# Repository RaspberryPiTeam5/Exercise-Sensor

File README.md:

This repository was created for a project using the raspberry pi. Files included are a schematic of the PCB used in conjunction with the pi along with the necessary files to run a GUI to plot outputs.  
Sensors used include:

1- Temperature Sensor

2- Moisture/Sweat Sensor

3- Pulse/Heart Rate Sensor  

The software requires the download of the qt4 and qwt libraries including:

   • qt4-dev-tools
   
   • libqt4-dev
   
   • libqwt-dev

To run the software:  
1- Clone the repository onto your pi with the following link: https://github.com/RaspberryPiTeam5/Exercise-Sensor  
2- build with the command "qmake" followed by "make"  
3- Run the program with "startx ./Exercise" (assuming no X is running whilst on an SSH).  
    
If you require any assistance with regards to this project, please contact either:  

Mustafa Miyasar - 2015221M@student.glasgow.ac.uk  
Roheel Arshad - 2018987A@student.glasgow.ac.uk
 
Please read the corresponding Wiki page for further information regarding this project.

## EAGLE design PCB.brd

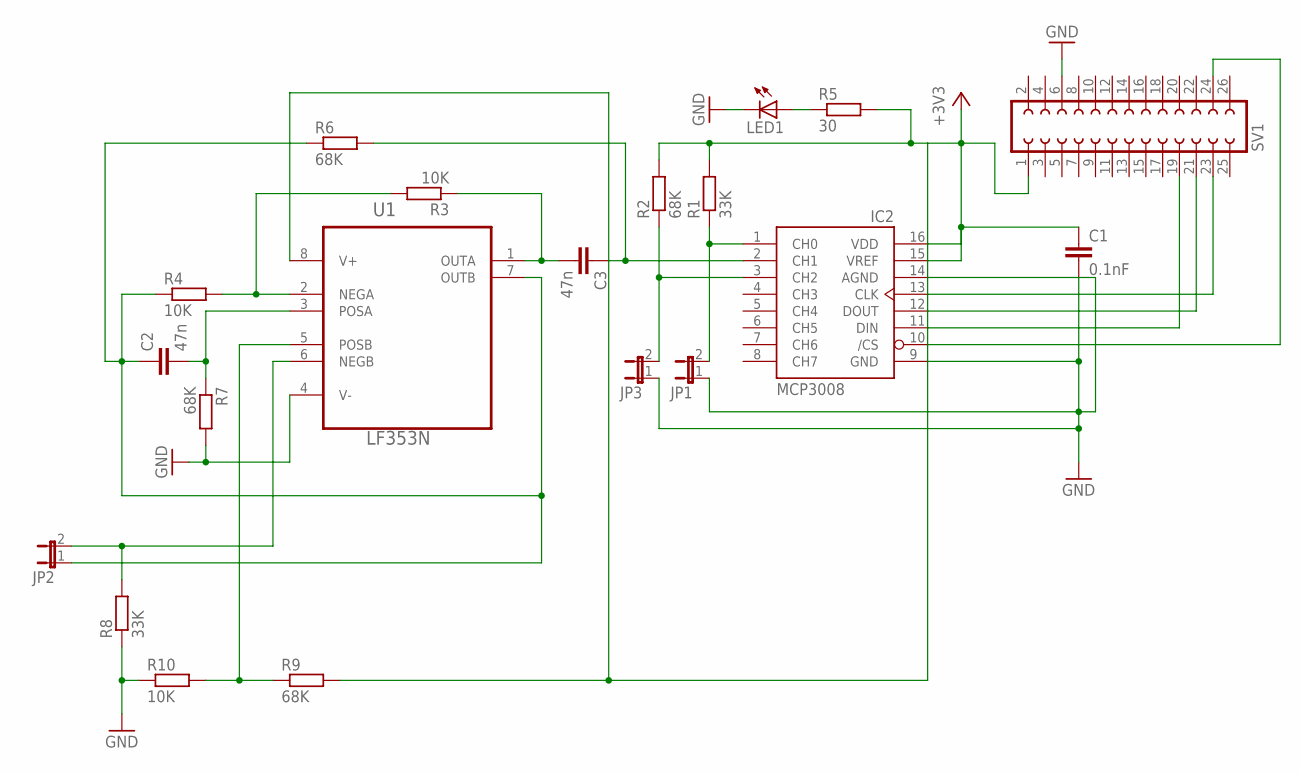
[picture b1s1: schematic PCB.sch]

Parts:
C1: 0.1nF; C050-035X075
C2, C3: 47n; C2.5-5
IC2: MCP3008; DIL16
JP1, JP2, JP3: JP1E; JP1
LED1: LED5MM
R1, R8: 33K; 0207/10
R2, R6, R7, R9: 68K; 0207/10
R3, R4, R10: 10K; 0207/10
R5: 30; 0207/10
SV1: FE13-2
U1: LF353N; DIP254P762X508-8

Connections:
+3.3V: C1.1, IC2.15 (VREF), IC2.16 (VDD), R1.2, R2.2, R5.2, R9.2, SV1.1, U1.8 (V+)
GND: C1.2, IC2.9 (GND), IC2.14 (AGND), JP1.1, JP3.1, LED1.K (C), R7.2, R8.1, R10.1, SV1.6, U1.4 (V-)
unnamed: IC2.10 (/CS), SV1.24
unnamed: IC2.13 (CLK), SV1.23
unnamed: IC2.11 (DIN), SV1.19
unnamed: IC2.12 (DOUT), SV1.21
unnamed: C2.2, R7.1, U1.3 (POSA)
unnamed: IC2.1 (CH0), JP1.2, R1.1
unnamed: LED1.A, R5.1
unnamed: R9.1, R10.2, U1.5 (POSB)
unnamed: JP2.2, R8.2, U1.6 (NEGB)
unnamed: IC2.3 (CH2), JP3.2, R2.1
unnamed: R3.2, R4.2, U1.2 (NEGA)
unnamed: C3.2, R3.1, U1.1 (OUTA)
unnamed: C3.1, IC2.2 (CH1), R6.2
unnamed: C2.1, JP2.1, R4.1, R6.1, U1.7 (OUTB)

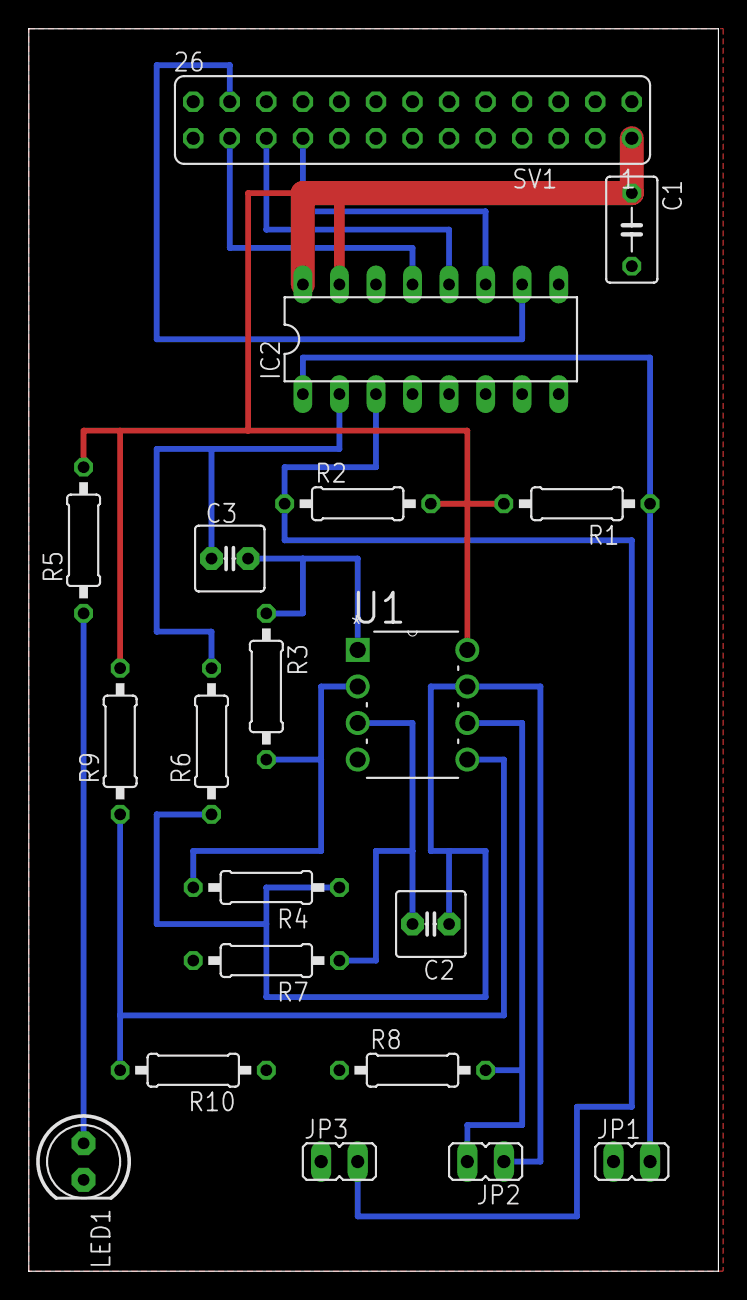
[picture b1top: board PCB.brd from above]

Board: 2 copper layers, 47.9 x 86.4 mm, 20 parts (0 on the bottom side), 16 nets.

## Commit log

2017-03-28 testing
2017-03-28 testing again
2017-03-28 this is jsut to show roheel
2017-03-28 adding ADC stuff
2017-03-28 Removing some unwanted files
2017-04-03 for the group
2017-04-05 Three plots and some code done
2017-04-05 Rename mcp3008SpiTest.cpp to ADCreader.cpp
2017-04-05 ADCreader header is here
2017-04-05 Moving out of folder
2017-04-05 Don't need really
2017-04-05 Updating for 3 channels
2017-04-05 Updating outputs for pi to work
2017-04-05 Hopefully it works now
2017-04-05 debugging
2017-04-05 Working atleast
2017-04-06 Changing axis around
2017-04-06 Changing axis again
2017-04-06 Temperature conversion works now
2017-04-07 Unit conversion for moisture and pulse
2017-04-07 Removing
2017-04-07 Changing units
2017-04-07 Adding buttons and knob gain
2017-04-07 Adding buttons and knob
2017-04-10 Copyright
2017-04-11 Update ADCreader.h
    changed int to float (Data0-2 & output0-1)
2017-04-11 Update README.md
    Added more useful information, easier to read
    Still need to add contact details, maybe more explanation about the PCB design? --> info will be on the wiki (Link that once finished!)
2017-04-11 Create LICENSE
2017-04-12 commenting
2017-04-12 comments
2017-04-12 Update window.cpp
    changed names of buttons
2017-04-12 mustafa changed this
2017-04-12 No he didnt
